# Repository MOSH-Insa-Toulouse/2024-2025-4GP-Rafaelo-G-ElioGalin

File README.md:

# 2024-2025-4GP-Rafaelo-G-ElioGalin

# Projet Capteur

## Somaire

- [Principe du Projet](#principe-du-projet)
- [Livrables](#livrables)
- [LTSpice](#ltspice)
- [Réalisation informatique du PCB sur KiCAD](#Realisation-informatique-du-pcb-sur-kicad)
- [Réalisation physique du PCB](#Réalisation-physique-du-PCB)
- [Code Arduino](#code-arduino)
- [Application](#application)
- [Datasheet](#datasheet)
- [Conclusion](#conclusion)
- [Auteurs](#auteurs)

## Contexte du Projet
Dans le Cadre du cours " Du capteur au banc de test", qui se base sur l'article "Pencil Drawn Strain Gauges and Chemiresistors on Paper" de Cheng-Wei Lin et al., les étudiants sont invités à caractériser un capteur particulier composé d'une simple feuille de papier et d'une couche de graphite. Cette couche de graphite joue le rôle d'une resistance variable qui dépend de la flexion du papier. Le but de ce projet est de réaliser un banc de test permettant d'étudier les variations de cette résistance en fonction de la déformation du capteur.

## Livrables

- Un PCB contenant différents modules se reliant à une carte Arduino UNO.
- Un code Arduino pour pouvoir controler les différents modules sur le PCB.
- Un application permettant la connection au PCB par Bluetooth.
- Une datasheet du capteur graphite.

## LTSpice 

La résistance du capteur graphite est de l'ordre du Méga Ohm et ne peut donc pas se mesurer simplemen. Nous utilison une alimentation 5V, nous avons donc :
U = R * I --> I = U/R --> I très faible.

Pour pouvoir obtenir des valeurs acceptables, nous avons réalisé un circuit amplificateur à transimpédance : 

Pour l'amplificateur opérationnel nécessaire au circuit, nous avons choisi le LTC1050 pour sa capacité à accepter un courant d'entrée faible et un offset de tension bas.

Afin d'améliorer le rapport Signal/Bruit, nous avons ajouté trois filtres : 

- filtre passe bas passif en entrée (R1,C1) avec une fréquence de coupure fc1 = 16Hz.
- filtre passe bas actif couplé à l'amplificateur opérationnel (R3,C4) avec une Fréquence de coupure fc2 = 1.6Hz. Ce filtre permet de s'isoler du bruit 50Hz du réseau électrique.
- filtre en sortie (R6,C2), avec une fréquence de coupure fc3 = 1.6kHz. Ce filtre permet de s'affranchir du bruit généré par notre circuit.

## Réalisation informatique du PCB sur KiCAD

Pour la réalisation du PCB, nous avons utilisé le logiciel KiCAD 6.0. Ce logiciel permet de créer le cricuit électrique ainsi que le PCB grâce à ses nombreuses librairies de composants.

La réalisation du PCB implique l'utilisation de différents modules qu'il faut pouvoir afficher sur le shéma : 

- Un module Bluetooth HC-05.
- Un écran OLED
- Un potentiomètre digital qui remplace la résistance R2 de notre circuit LTSpice.

Dans un premier temps, nous avons effectuée le shéma électrique : 

Dans un second temps, une fois tous les composants reliés entre eux, nous avons réalisé le PCB :

Voici un visuel 3D du PCB pour donner une idée du placement des composants :

Vous pouvez tout retrouver en détail dans le dossier [Kicad](/kicad/).

## Réalisation physique du PCB

Grâce à l'aide de Catherine Crouzet, nous avons pu fabriquer le PCB nous mêmes.

Pour ce faire, nous avons tout d'abord créé un fichier Gerber depuis KiCAD :

Ce filtre sert de masque de gravure. On place le masque sur une plaquette en epoxy jaune recouverte d'une fine couche de cuivre, elle même recouverte d'une couche de résine. Il sert de porotection pour la résine lors de son passage sous une lampe UV. Apres son passage sous la lampe à UV, la plaquette est déposé dans un bain "révélateur", qui retire la couche de résine qui a été en contact avec les UV, et aussi le cuivre en dessous de cette résine. Après un contrôle visuel pour s'assurer de la bonne exécution du processus, la plaque est retiré du bain et lavée à l'eau pour retirer le produit du bain et ensuite à l'acétone pour retirer la couche de résine qui a protégé les pistes en cuivre. Le PCB est maintenant près, on peut couper les parties non nécessaire de la carte pour un rendu plus propre.

Suite à ce processus, nous avons percé les trous dans lesquels des composants ainsi que des connecteurs des différents modules, puis nous les avons soudés.

## Code Arduino

Les differents modules sont contrôlés par un code Arduino 

Au branchement de l'Arduino UNO, après avoir envoyé le code, on peut voir sur l'écran OLED un menu déroulant:

-Menu 1 : Mesure Graphite
-Menu 2 : Infos Createurs

La navigation se fait avec l'encodeur rotatoir, le faire tourner permets de faire defiler les menus, et le cliquer permet d'accéder au menu sélectionné.

Vous trouverez le code Arduino [ici](/Code-Arduino/)

## Application

Nous avons utilisé  le site MIT App Inventor pour réalisé l'application qui reçoit et affiche en temps réel les valeurs mesurées par le Capeur graphite sur un graphe.

PHOTO

L'application est assez simple. Elle permet :
- De se connecter à un appareil via le bluetooth.
- De démarrer une acquisition et de la mettre en pause.
- d'effacer le graphe.
- De s'adapter en cas de changement de position du téléphone en offrant un mode paysage.

Vous la trouverez [ici](/Application Projet Capteur/)

## Datasheet

Nous avons écrit une datasheet qui caractérise le capteur graphite. Nous avons réalisé les mesures avec notre système et à l'aide d'un module 3D composé de demi-cercles permettant une déformation croissante précise.

Nous avons pu tracer ces courbes caractéristique de différents types de crayons (2H,HB,2B,4B,6B): 

Compression :

Tension:

Vous pouvez retrouver cette datasheet [ici](/Datasheet/)

## Conclusion

Tous nos résultats sont à  prendre avec prudence. Nous ne pouvons pas affirmer avoir réalisé un dépot de graphite parfaitement uniforme sur tous les capteurs, ce qui a pu avoir un impact important sur la valeur de leur résistance, et donc sur leur comprtement. De plus, la qualité du matériel utilisé n'est pas  optimale : les composants et les connexions présentent des imperfections qui ont pu influencer les mesures obtenues.

Cela dit, ce capteur présente plusieurs avantages : il est très versatile, peu coûteux, et extrêmement simple d’utilisation. L’électronique associée peut être facilement miniaturisée, et le capteur s’avère relativement sensible. Son principal défaut reste cependant l’homogénéité du dépôt de graphite. Si ce point pouvait être amélioré, le capteur pourrait être envisagé pour des applications industrielles, notamment pour des usages ponctuels, à grande échelle, ou à usage unique.
Dans un cadre personnel ou éducatif, ce capteur est particulièrement adapté. Il possède une forte valeur pédagogique, comme en témoigne ce projet, en permettant d’explorer de nombreux domaines scientifiques et techniques.

Ce capteur est-il industrialisable ? 

Oui et non.

Il pourrait trouver une application dans des secteurs comme l’aviation, où l’on utilise un très grand nombre de capteurs de contrainte. Son faible coût pourrait représenter un avantage économique. Néanmoins, ses limitations électroniques — notamment en termes de fiabilité et de miniaturisation — pourraient poser problème dans des environnements contraints.

Il pourrait en revanche être largement démocratisé dans le domaine de l’éducation, comme outil d’apprentissage ou de découverte.

Mais malgré son coût très faible, ce capteur reste très niche et la présence d’options plus performantes sur le marché rendent sa rentabilité à l'échelle industrielle peu crédible. Nous pensons donc qu’il serait difficilement industrialisable à grande échelle.

## Auteurs

Rafaëlo GERARDIN : <gerardin@insa-toulouse.fr>
Elio GALIN : <galin@insa-toulouse.fr>

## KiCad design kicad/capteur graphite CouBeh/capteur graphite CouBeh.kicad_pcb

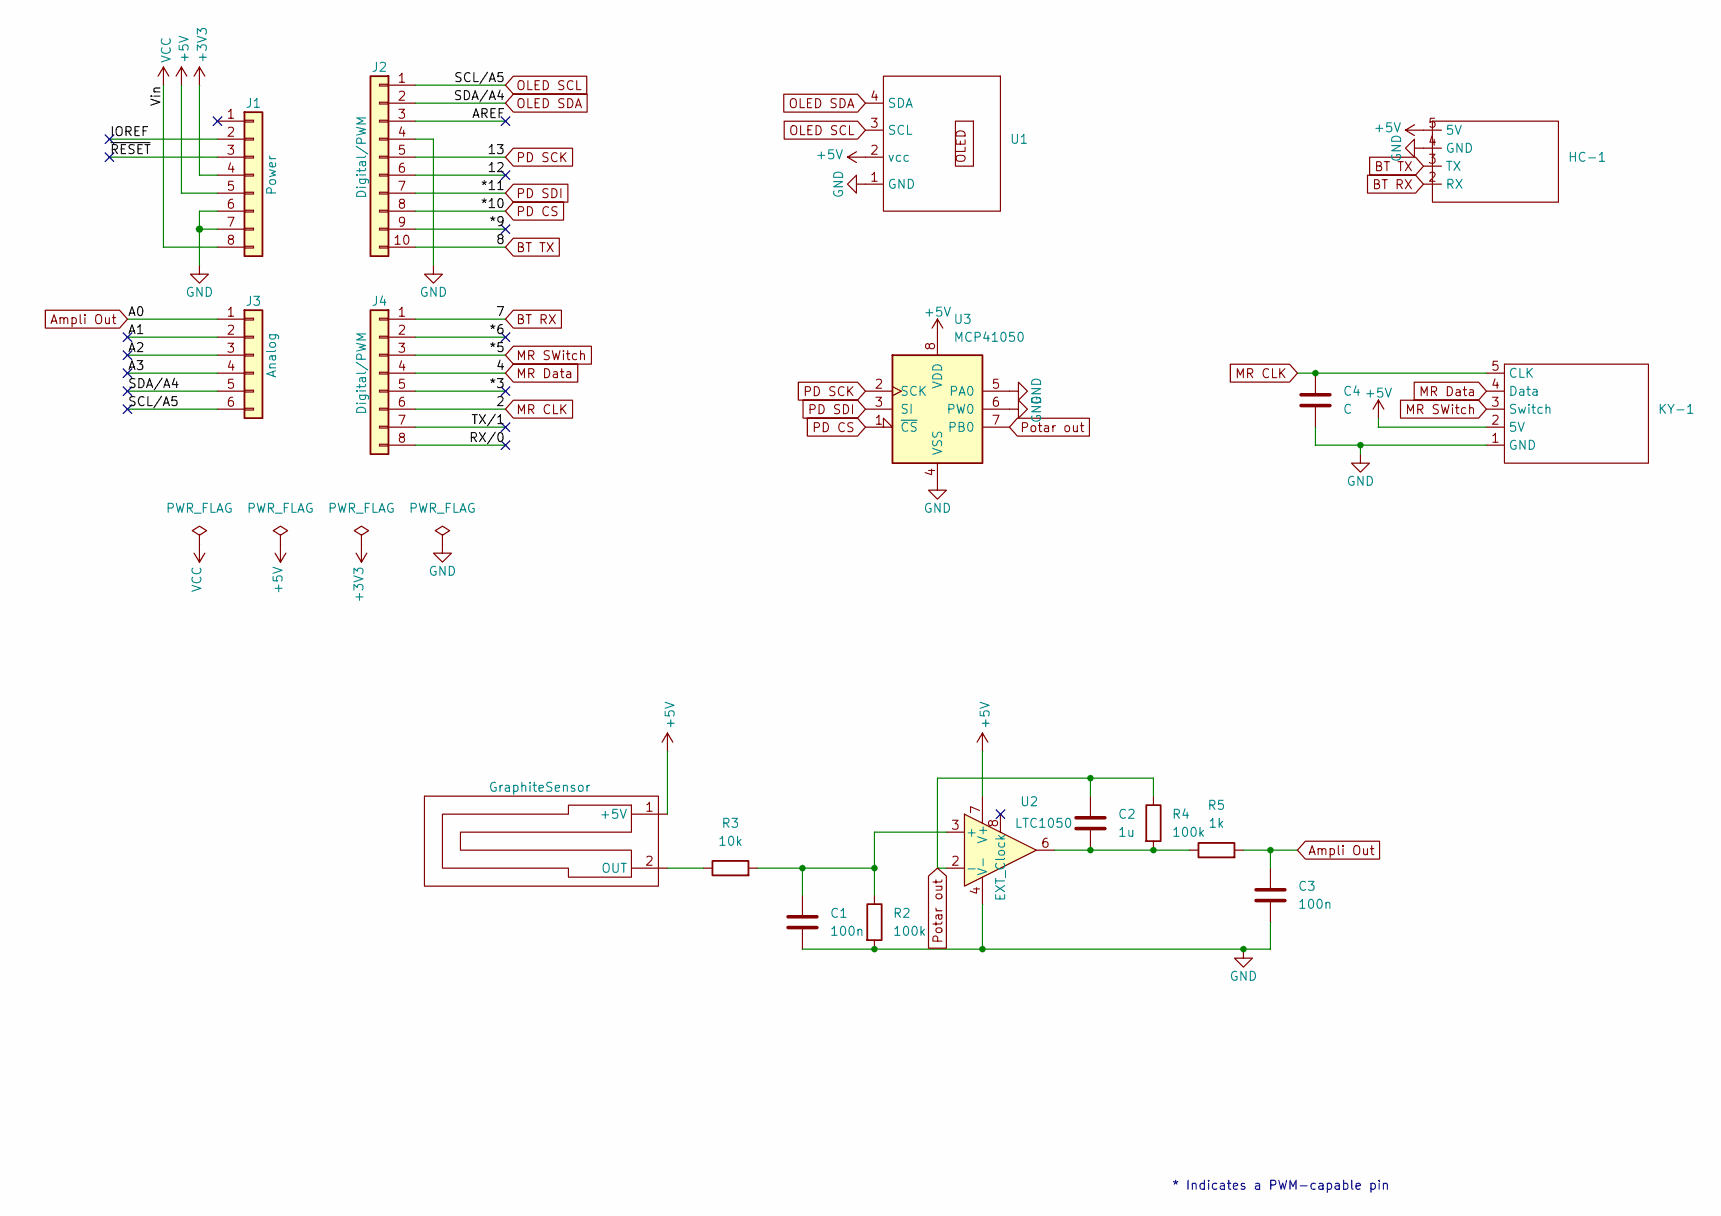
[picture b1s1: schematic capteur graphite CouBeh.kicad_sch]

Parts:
C1, C3: 100n; C_Disc_D3.0mm_W2.0mm_P2.50mm
C2: 1u; C_Rect_L7.0mm_W4.5mm_P5.00mm
C4: C; C_Disc_D3.0mm_W2.0mm_P2.50mm
GraphiteSensor: (no value)
HC-1: Module Bluetooth
J1: Power; PinSocket_1x08_P2.54mm_Vertical
J2: Digital/PWM; PinSocket_1x10_P2.54mm_Vertical
J3: Analog; PinSocket_1x06_P2.54mm_Vertical
J4: Digital/PWM; PinSocket_1x08_P2.54mm_Vertical
KY-1: Module Rotatoire
R2, R4: 100k; R_Axial_DIN0207_L6.3mm_D2.5mm_P10.16mm_Horizontal
R3: 10k; R_Axial_DIN0207_L6.3mm_D2.5mm_P10.16mm_Horizontal
R5: 1k; R_Axial_DIN0204_L3.6mm_D1.6mm_P7.62mm_Horizontal
U1: OLED
U2: LTC1050; DIP-8_W7.62mm
U3: MCP41050; PDIP8_300MC_MCH

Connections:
+3V3: J1.4
+5V: GraphiteSensor.1 (+5V), HC-1.5 (5V), J1.5, KY-1.2 (5V), U1.2 (vcc), U2.7 (V+), U3.8 (VDD); also elsewhere on the board
/12: J2.6
/*3: J4.5
/*6: J4.2
/*9: J2.9
/A1: J3.2
/A2: J3.3
/A3: J3.4
/AREF: J2.3
/IOREF: J1.2
/RX/0: J4.8
/TX/1: J4.7
/~RESET: J1.3
Ampli Out: C3.1, J3.1, R5.2
BT RX: HC-1.2 (RX), J4.1
BT TX: HC-1.3 (TX), J2.10
GND: C1.2, C3.2, C4.2, HC-1.4 (GND), J1.6, J1.7, J2.4, KY-1.1 (GND), R2.2, U1.1 (GND), U2.4 (V-), U3.4 (VSS), U3.5 (PA0), U3.6 (PW0)
MR CLK: C4.1, J4.6, KY-1.5 (CLK)
MR Data: J4.4, KY-1.4 (Data)
MR SWitch: J4.3, KY-1.3 (Switch)
unnamed: C2.2, R4.2, R5.1, U2.6
unnamed 22: GraphiteSensor.2 (OUT), R3.1; also elsewhere on the board
unnamed: C1.1, R2.1, R3.2, U2.3 (+)
OLED SCL: J2.1, J3.6, U1.3 (SCL)
OLED SDA: J2.2, J3.5, U1.4 (SDA)
PD CS: J2.8, U3.1 (~CS)
PD SCK: J2.5, U3.2 (SCK)
PD SDI: J2.7, U3.3 (SI)
Potar out: C2.1, R4.1, U2.2 (-), U3.7 (PB0)
VCC: J1.8

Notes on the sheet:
* Indicates a PWM-capable pin

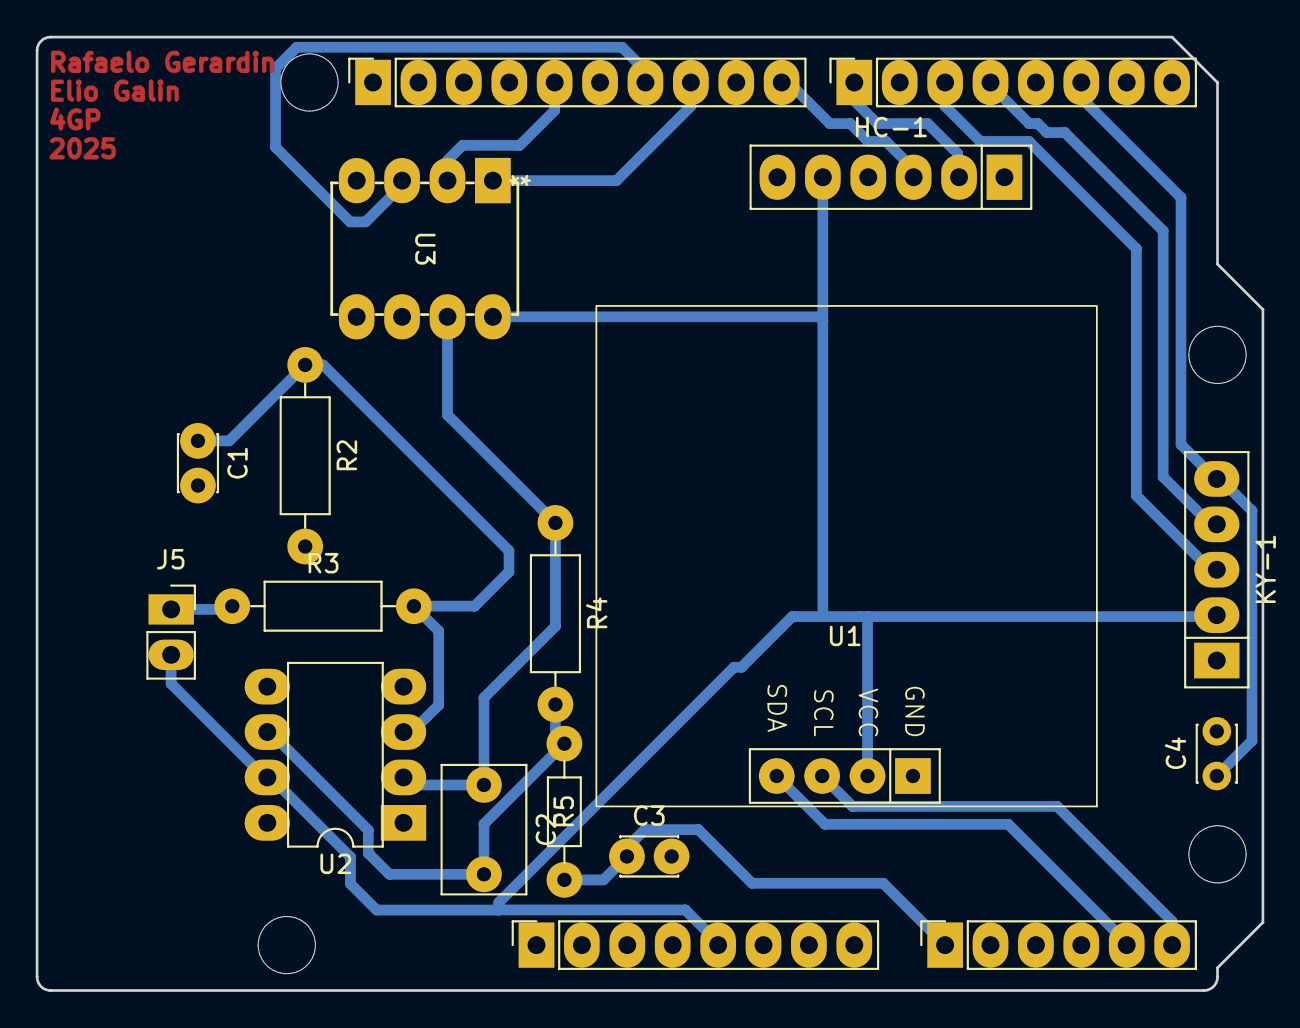
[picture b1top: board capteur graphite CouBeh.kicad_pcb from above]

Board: 2 copper layers, 68.6 x 53.3 mm, 22 parts (0 on the bottom side), 17 nets.

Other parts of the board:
J5: Conn_01x02; PinSocket_1x02_P2.54mm_Vertical
MH1, MH2, MH3, MH4: MountingHole_3.2mm

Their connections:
+5V: J5.2; also elsewhere on the board
unnamed 22: J5.1; also elsewhere on the board

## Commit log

2025-02-21 Ajout de ma to-do list
2025-02-21 Ajout d'un item a la liste
2025-05-22 Rename Circuit LTSpice.PNG to Circuit-LTSpice.PNG
2025-05-22 Rename Grape Flexion.PNG to Graphe-Flexion.PNG
2025-05-22 Rename Graphe compression.PNG to Graphe-compression.PNG
2025-05-22 Rename PCB Projet Capteur.PNG to PCB Projet-Capteur.PNG
2025-05-22 Rename PCB Projet-Capteur.PNG to PCB-Projet-Capteur.PNG
2025-05-22 Rename Vue 3D PCB.PNG to Vue-3D-PCB.PNG
2025-05-22 Rename Kicad photo.png to Kicad-photo.png
2025-05-22 Create Code Arduino
2025-05-22 Update Code Arduino
